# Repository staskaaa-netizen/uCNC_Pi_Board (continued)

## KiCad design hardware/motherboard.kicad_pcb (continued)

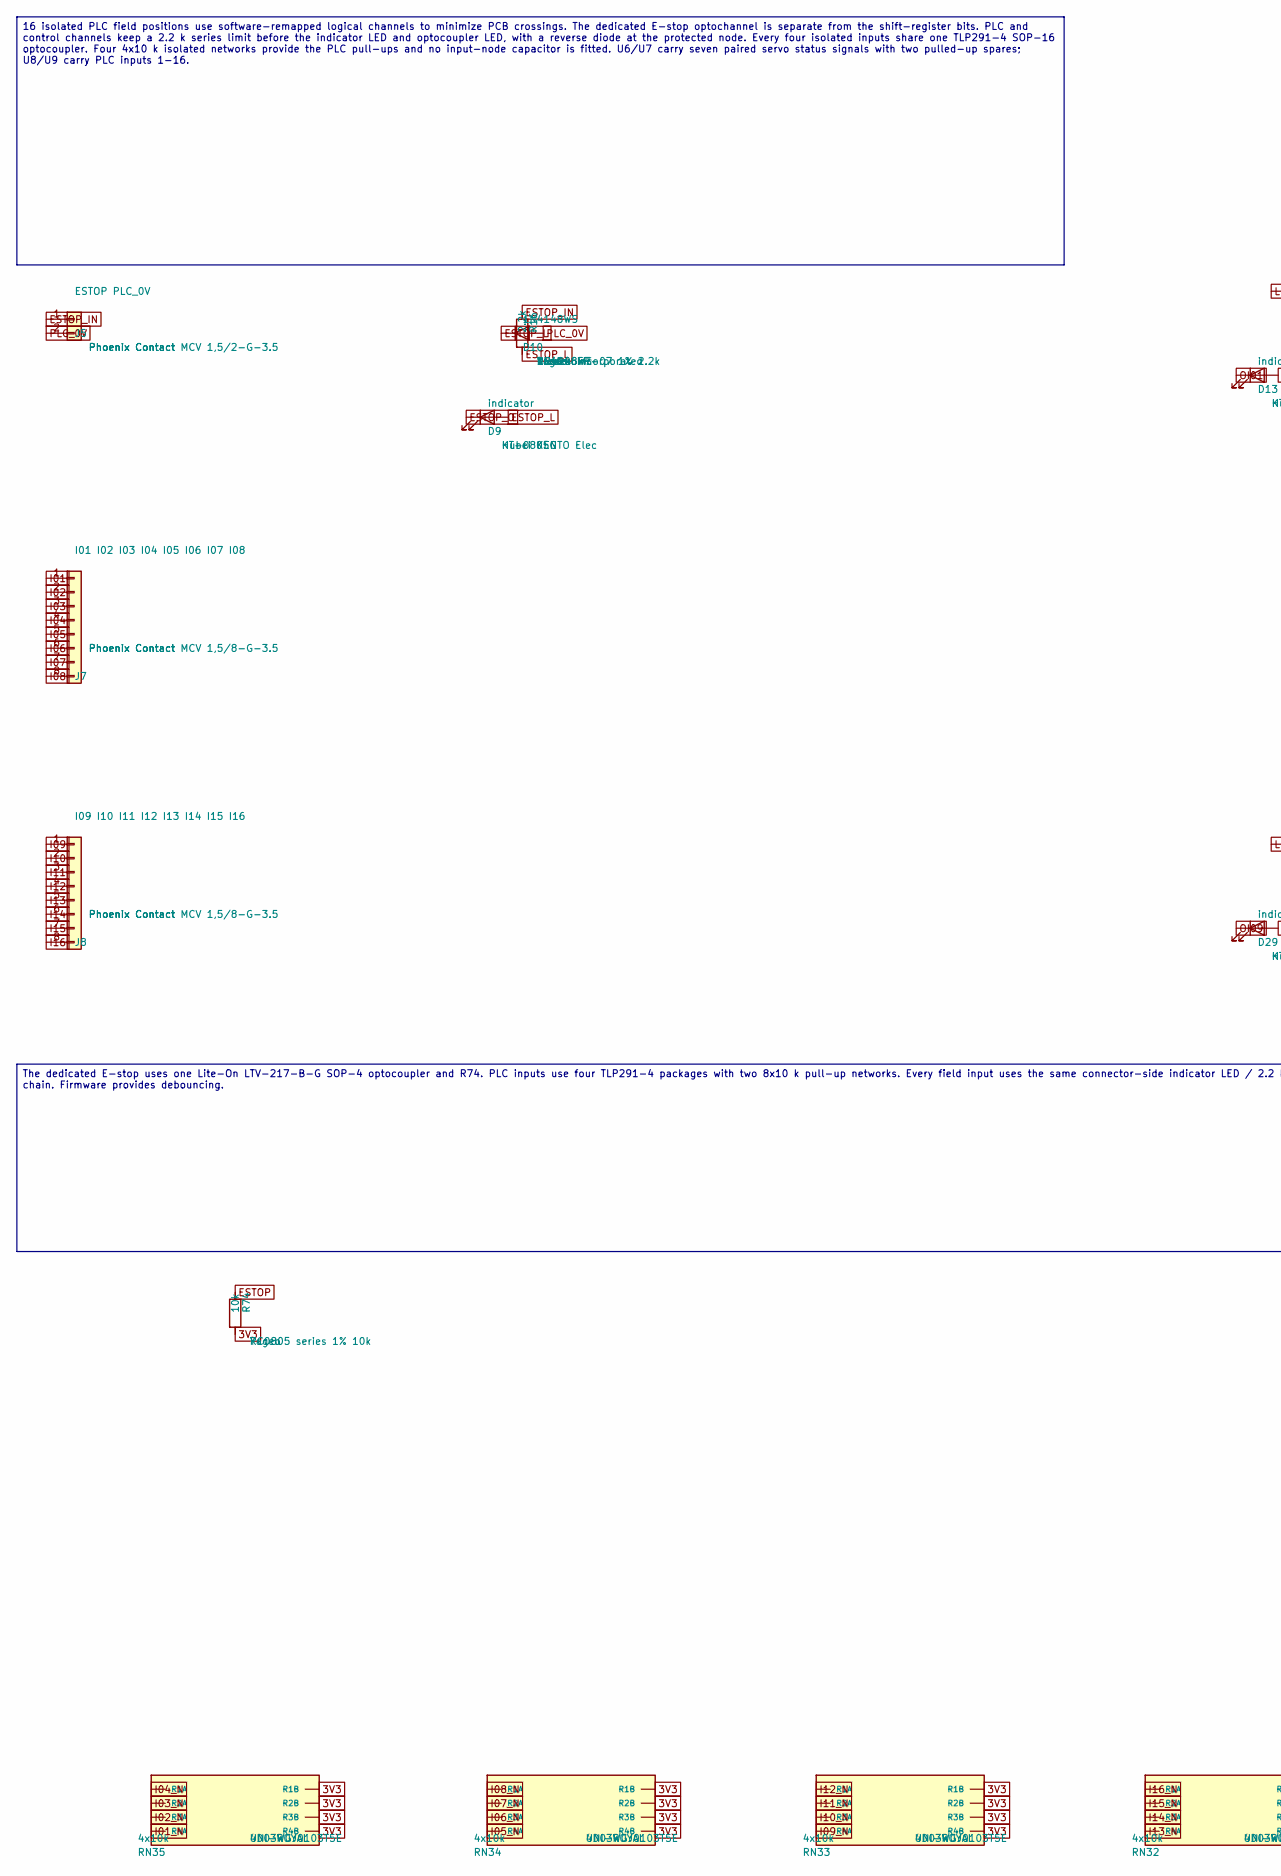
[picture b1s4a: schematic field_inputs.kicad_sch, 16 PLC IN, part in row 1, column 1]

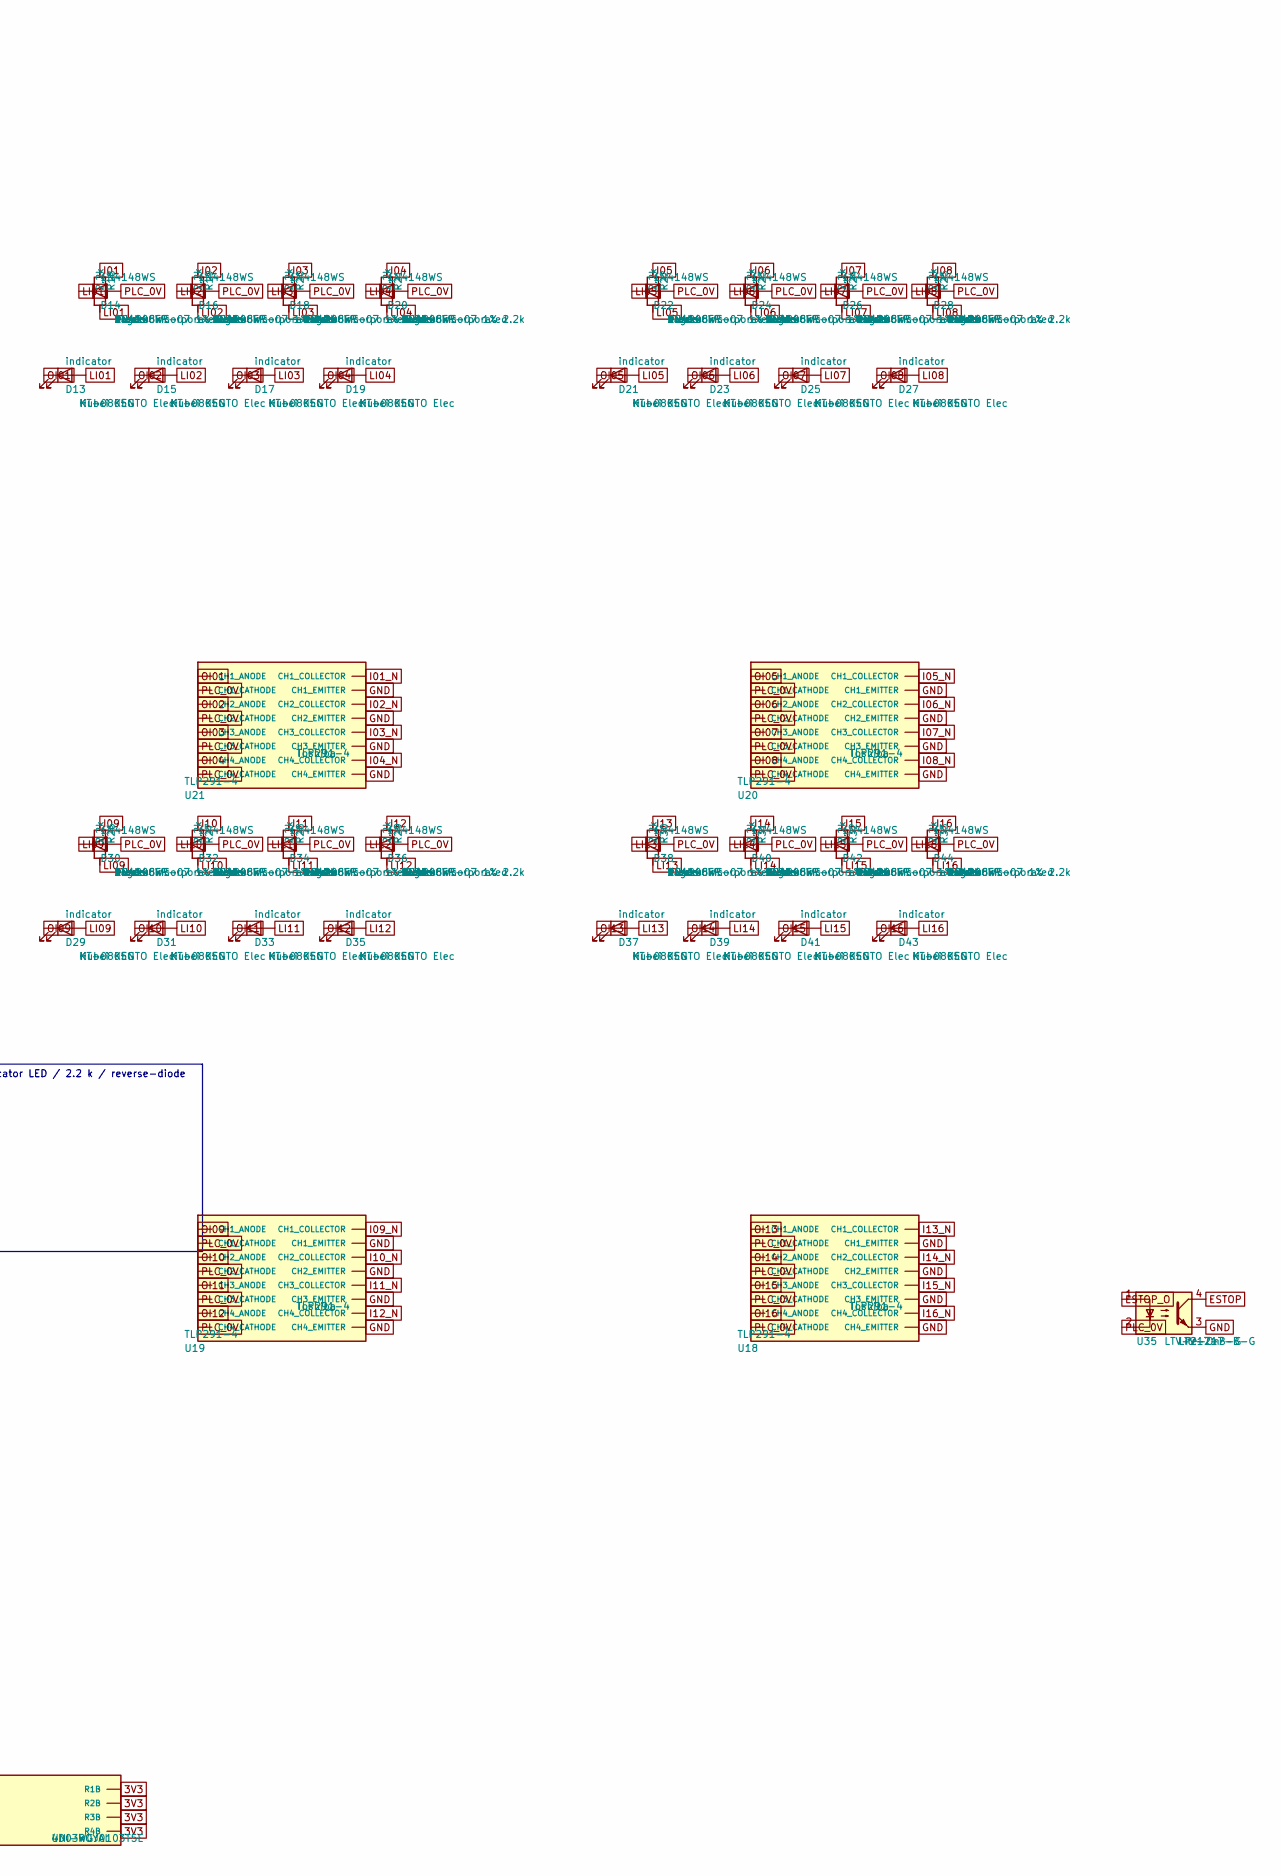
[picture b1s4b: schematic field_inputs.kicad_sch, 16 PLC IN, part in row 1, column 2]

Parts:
D9, D13, D15, D17, D19, D21, D23, D25, D27, D29, D31, D33, D35, D37, D39, D41, D43: indicator; LED_0805_2012Metric; MPN KT-0805G
D10, D14, D16, D18, D20, D22, D24, D26, D28, D30, D32, D34, D36, D38, D40, D42, D44: 1N4148WS; D_SOD-323; MPN 1N4148WS
J5: ESTOP PLC_0V; PhoenixContact_MCV_1,5_2-G-3.5_1x02_P3.50mm_Vertical; MPN Phoenix Contact MCV 1,5/2-G-3.5
J7: I01 I02 I03 I04 I05 I06 I07 I08; PhoenixContact_MCV_1,5_8-G-3.5_1x08_P3.50mm_Vertical; MPN Phoenix Contact MCV 1,5/8-G-3.5
J8: I09 I10 I11 I12 I13 I14 I15 I16; PhoenixContact_MCV_1,5_8-G-3.5_1x08_P3.50mm_Vertical; MPN Phoenix Contact MCV 1,5/8-G-3.5
R16, R18, R19, R20, R21, R22, R23, R24, R25, R26, R27, R28, R29, R30, R31, R32, R33: 2.2k; R_1206_3216Metric; MPN RC1206FR-07 1% 2.2k
R74: 10k; R_0805_2012Metric; MPN RC0805 series 1% 10k
RN32, RN33, RN34, RN35: 4x10k; R_Array_Convex_4x0603; MPN 4D03WGJ0103T5E
U18, U19, U20, U21: TLP291-4; SOIC-16_4.55x10.3mm_P1.27mm; MPN TLP291-4
U35: LTV-217-B-G; SOIC-4_4.55x2.6mm_P1.27mm; MPN LTV-217-B-G

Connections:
3V3: R74.2, RN32.5 (R4B), RN32.6 (R3B), RN32.7 (R2B), RN32.8 (R1B), RN33.5 (R4B), RN33.6 (R3B), RN33.7 (R2B), RN33.8 (R1B), RN34.5 (R4B), RN34.6 (R3B), RN34.7 (R2B), RN34.8 (R1B), RN35.5 (R4B), RN35.6 (R3B), RN35.7 (R2B), RN35.8 (R1B); also elsewhere on the board
ESTOP: R74.1, U35.4; also elsewhere on the board
ESTOP_IN: J5.1, R16.1
ESTOP_L: D9.2 (A), D10.1 (K), R16.2
ESTOP_O: D9.1 (K), U35.1
GND: U18.9 (CH4_EMITTER), U18.11 (CH3_EMITTER), U18.13 (CH2_EMITTER), U18.15 (CH1_EMITTER), U19.9 (CH4_EMITTER), U19.11 (CH3_EMITTER), U19.13 (CH2_EMITTER), U19.15 (CH1_EMITTER), U20.9 (CH4_EMITTER), U20.11 (CH3_EMITTER), U20.13 (CH2_EMITTER), U20.15 (CH1_EMITTER), U21.9 (CH4_EMITTER), U21.11 (CH3_EMITTER), U21.13 (CH2_EMITTER), U21.15 (CH1_EMITTER), U35.3; also elsewhere on the board
I01: J7.1, R18.1
I01_N: RN35.4 (R4A), U21.16 (CH1_COLLECTOR); also elsewhere on the board
I02: J7.2, R19.1
I02_N: RN35.3 (R3A), U21.14 (CH2_COLLECTOR); also elsewhere on the board
I03: J7.3, R20.1
I03_N: RN35.2 (R2A), U21.12 (CH3_COLLECTOR); also elsewhere on the board
I04: J7.4, R21.1
I04_N: RN35.1 (R1A), U21.10 (CH4_COLLECTOR); also elsewhere on the board
I05: J7.5, R22.1
I05_N: RN34.4 (R4A), U20.16 (CH1_COLLECTOR); also elsewhere on the board
I06: J7.6, R23.1
I06_N: RN34.3 (R3A), U20.14 (CH2_COLLECTOR); also elsewhere on the board
I07: J7.7, R24.1
I07_N: RN34.2 (R2A), U20.12 (CH3_COLLECTOR); also elsewhere on the board
I08: J7.8, R25.1
I08_N: RN34.1 (R1A), U20.10 (CH4_COLLECTOR); also elsewhere on the board
I09: J8.1, R26.1
I09_N: RN33.4 (R4A), U19.16 (CH1_COLLECTOR); also elsewhere on the board
I10: J8.2, R27.1
I10_N: RN33.3 (R3A), U19.14 (CH2_COLLECTOR); also elsewhere on the board
I11: J8.3, R28.1
I11_N: RN33.2 (R2A), U19.12 (CH3_COLLECTOR); also elsewhere on the board
I12: J8.4, R29.1
I12_N: RN33.1 (R1A), U19.10 (CH4_COLLECTOR); also elsewhere on the board
I13: J8.5, R30.1
I13_N: RN32.4 (R4A), U18.16 (CH1_COLLECTOR); also elsewhere on the board
I14: J8.6, R31.1
I14_N: RN32.3 (R3A), U18.14 (CH2_COLLECTOR); also elsewhere on the board
I15: J8.7, R32.1
I15_N: RN32.2 (R2A), U18.12 (CH3_COLLECTOR); also elsewhere on the board
I16: J8.8, R33.1
I16_N: RN32.1 (R1A), U18.10 (CH4_COLLECTOR); also elsewhere on the board
LI01: D13.2 (A), D14.1 (K), R18.2
LI02: D15.2 (A), D16.1 (K), R19.2
LI03: D17.2 (A), D18.1 (K), R20.2
LI04: D19.2 (A), D20.1 (K), R21.2
LI05: D21.2 (A), D22.1 (K), R22.2
LI06: D23.2 (A), D24.1 (K), R23.2
LI07: D25.2 (A), D26.1 (K), R24.2
LI08: D27.2 (A), D28.1 (K), R25.2
LI09: D29.2 (A), D30.1 (K), R26.2
LI10: D31.2 (A), D32.1 (K), R27.2
LI11: D33.2 (A), D34.1 (K), R28.2
LI12: D35.2 (A), D36.1 (K), R29.2
LI13: D37.2 (A), D38.1 (K), R30.2
LI14: D39.2 (A), D40.1 (K), R31.2
LI15: D41.2 (A), D42.1 (K), R32.2
LI16: D43.2 (A), D44.1 (K), R33.2
OI01: D13.1 (K), U21.1 (CH1_ANODE)
OI02: D15.1 (K), U21.3 (CH2_ANODE)
OI03: D17.1 (K), U21.5 (CH3_ANODE)
OI04: D19.1 (K), U21.7 (CH4_ANODE)
OI05: D21.1 (K), U20.1 (CH1_ANODE)
OI06: D23.1 (K), U20.3 (CH2_ANODE)
OI07: D25.1 (K), U20.5 (CH3_ANODE)
OI08: D27.1 (K), U20.7 (CH4_ANODE)
OI09: D29.1 (K), U19.1 (CH1_ANODE)
OI10: D31.1 (K), U19.3 (CH2_ANODE)
OI11: D33.1 (K), U19.5 (CH3_ANODE)
OI12: D35.1 (K), U19.7 (CH4_ANODE)
OI13: D37.1 (K), U18.1 (CH1_ANODE)
OI14: D39.1 (K), U18.3 (CH2_ANODE)
OI15: D41.1 (K), U18.5 (CH3_ANODE)
OI16: D43.1 (K), U18.7 (CH4_ANODE)
PLC_0V: D10.2 (A), D14.2 (A), D16.2 (A), D18.2 (A), D20.2 (A), D22.2 (A), D24.2 (A), D26.2 (A), D28.2 (A), D30.2 (A), D32.2 (A), D34.2 (A), D36.2 (A), D38.2 (A), D40.2 (A), D42.2 (A), D44.2 (A), J5.2, U18.2 (CH1_CATHODE), U18.4 (CH2_CATHODE), U18.6 (CH3_CATHODE), U18.8 (CH4_CATHODE), U19.2 (CH1_CATHODE), U19.4 (CH2_CATHODE), U19.6 (CH3_CATHODE), U19.8 (CH4_CATHODE), U20.2 (CH1_CATHODE), U20.4 (CH2_CATHODE), U20.6 (CH3_CATHODE), U20.8 (CH4_CATHODE), U21.2 (CH1_CATHODE), U21.4 (CH2_CATHODE), U21.6 (CH3_CATHODE), U21.8 (CH4_CATHODE), U35.2; also elsewhere on the board

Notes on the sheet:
16 isolated PLC field positions use software-remapped logical channels to minimize PCB crossings. The dedicated E-stop optochannel is separate from the shift-register bits. PLC and control channels keep a 2.2 k series limit before the indicator LED and optocoupler LED, with a reverse diode at the p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
The dedicated E-stop uses one Lite-On LTV-217-B-G SOP-4 optocoupler and R74. PLC inputs use four TLP291-4 packages with two 8x10 k pull-up networks. Every field input uses the same connector-side indicator LED / 2.2 k / reverse-diode chain. Firmware provides debouncing.

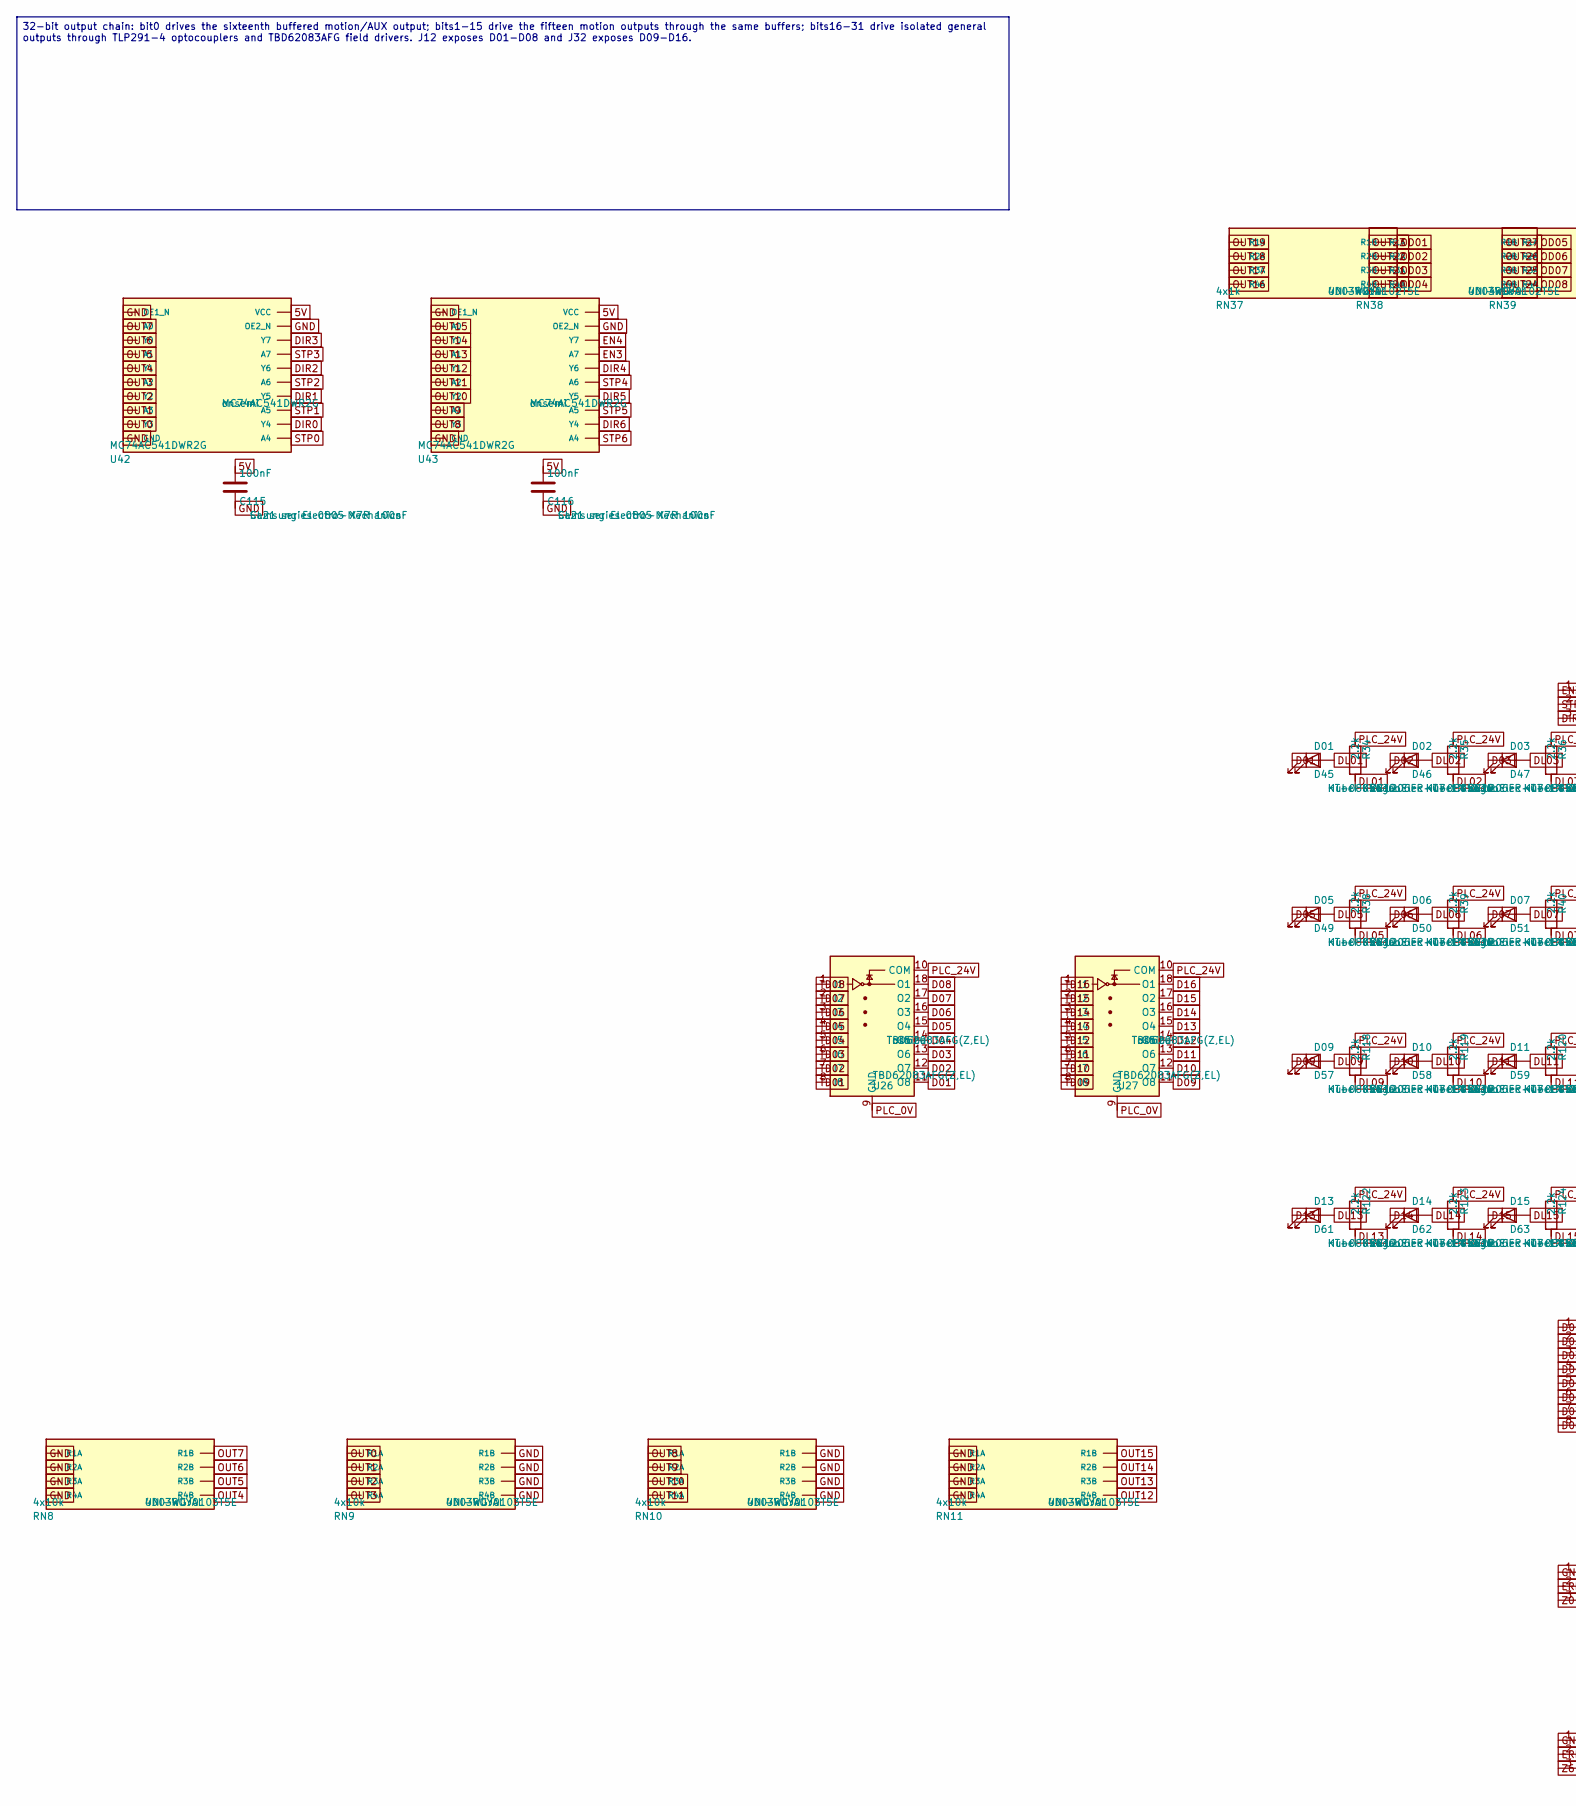
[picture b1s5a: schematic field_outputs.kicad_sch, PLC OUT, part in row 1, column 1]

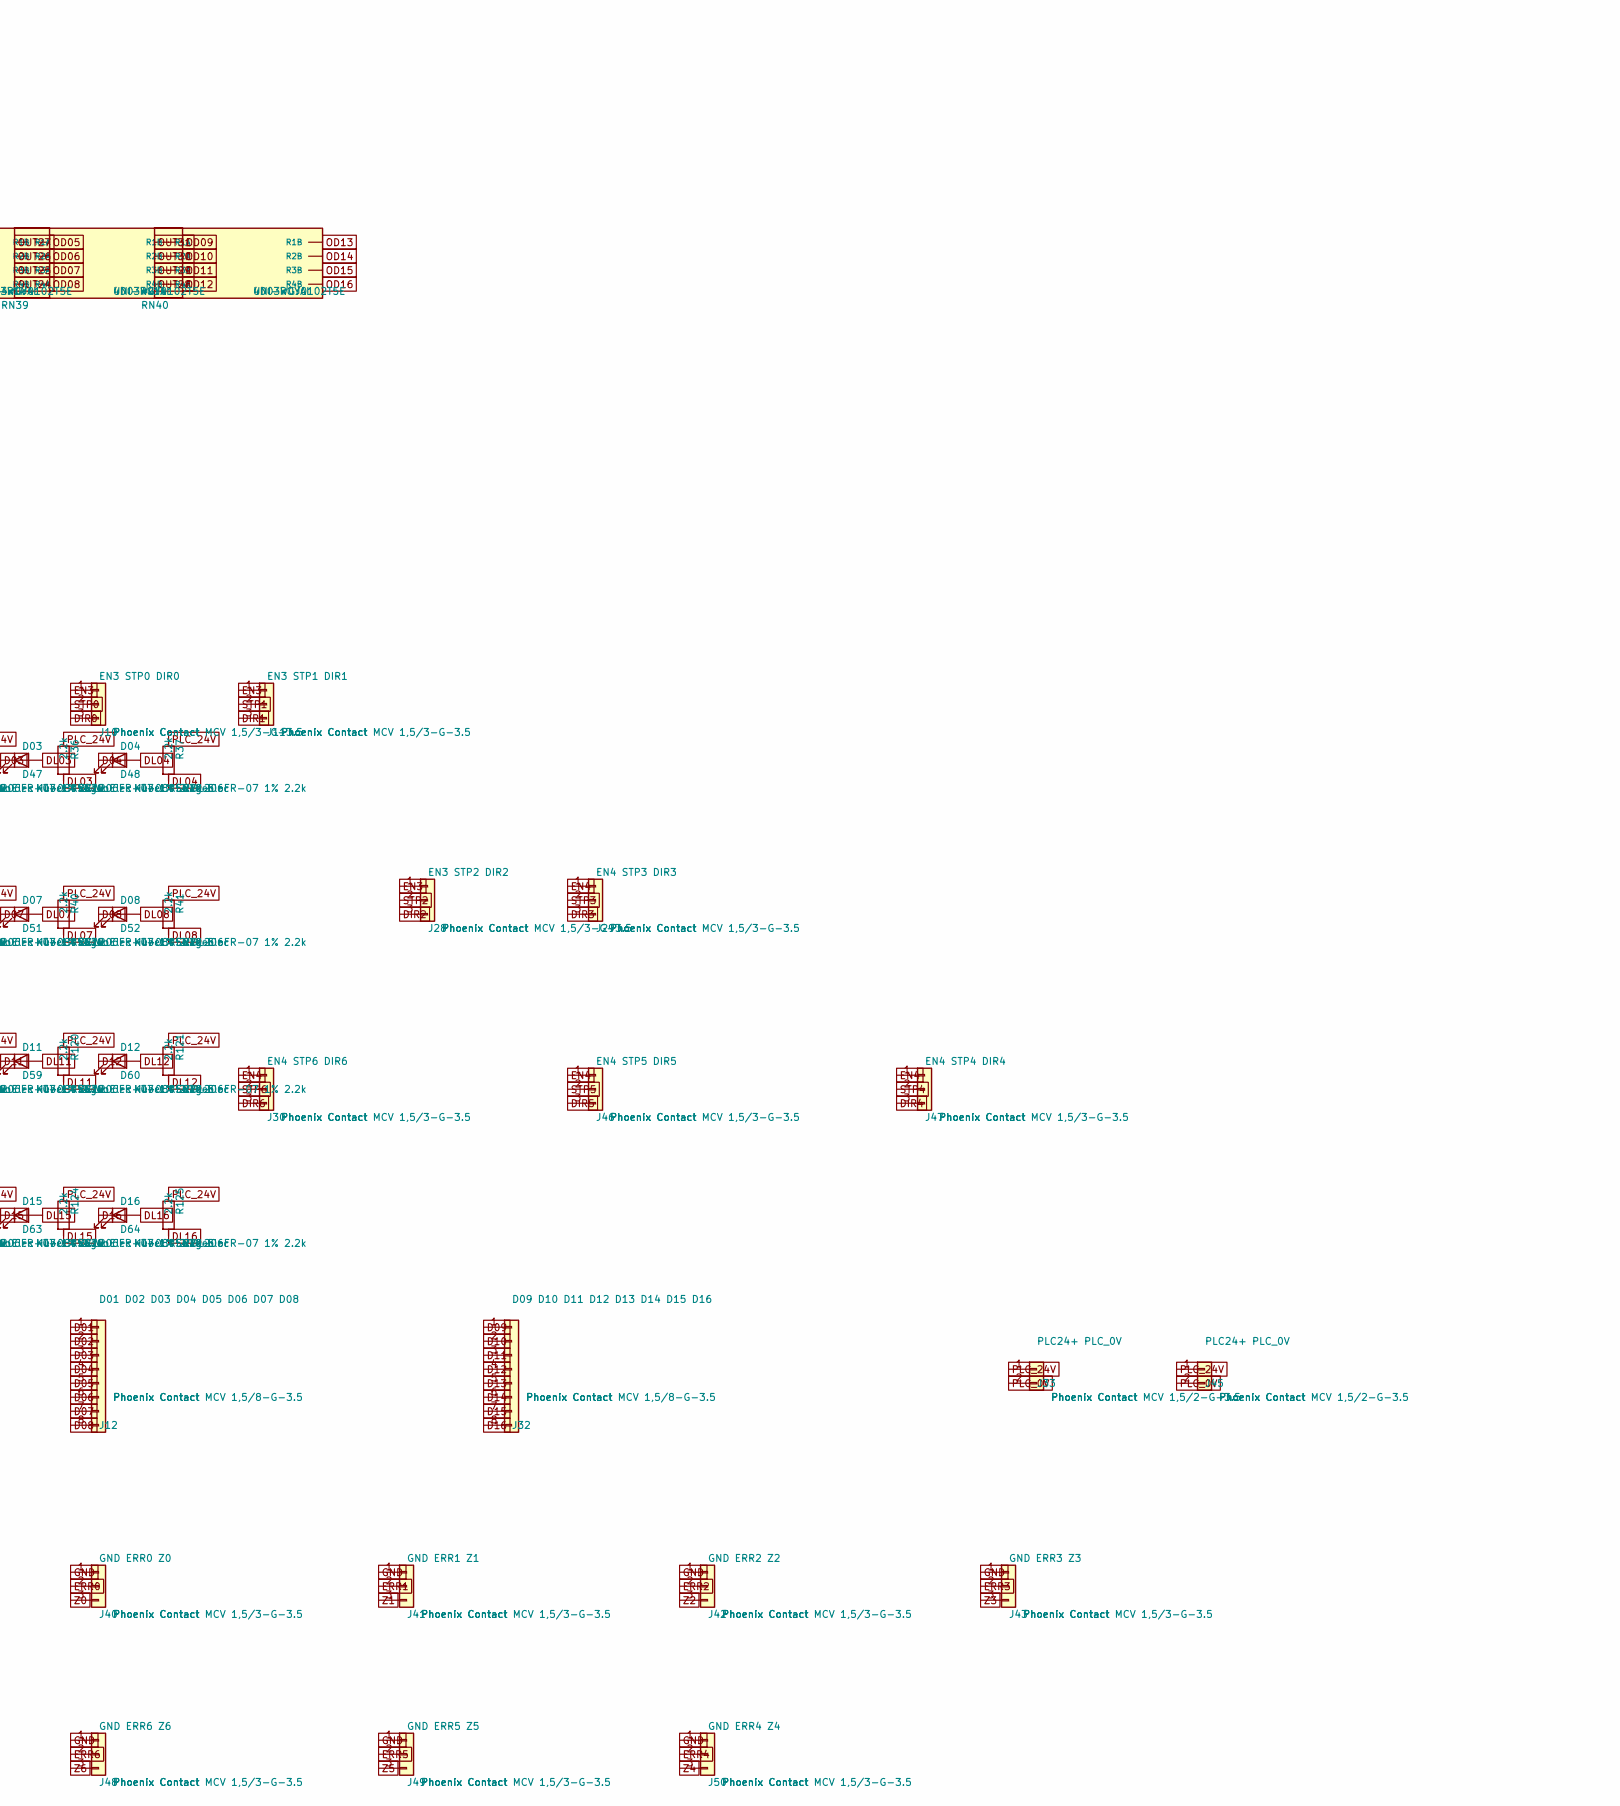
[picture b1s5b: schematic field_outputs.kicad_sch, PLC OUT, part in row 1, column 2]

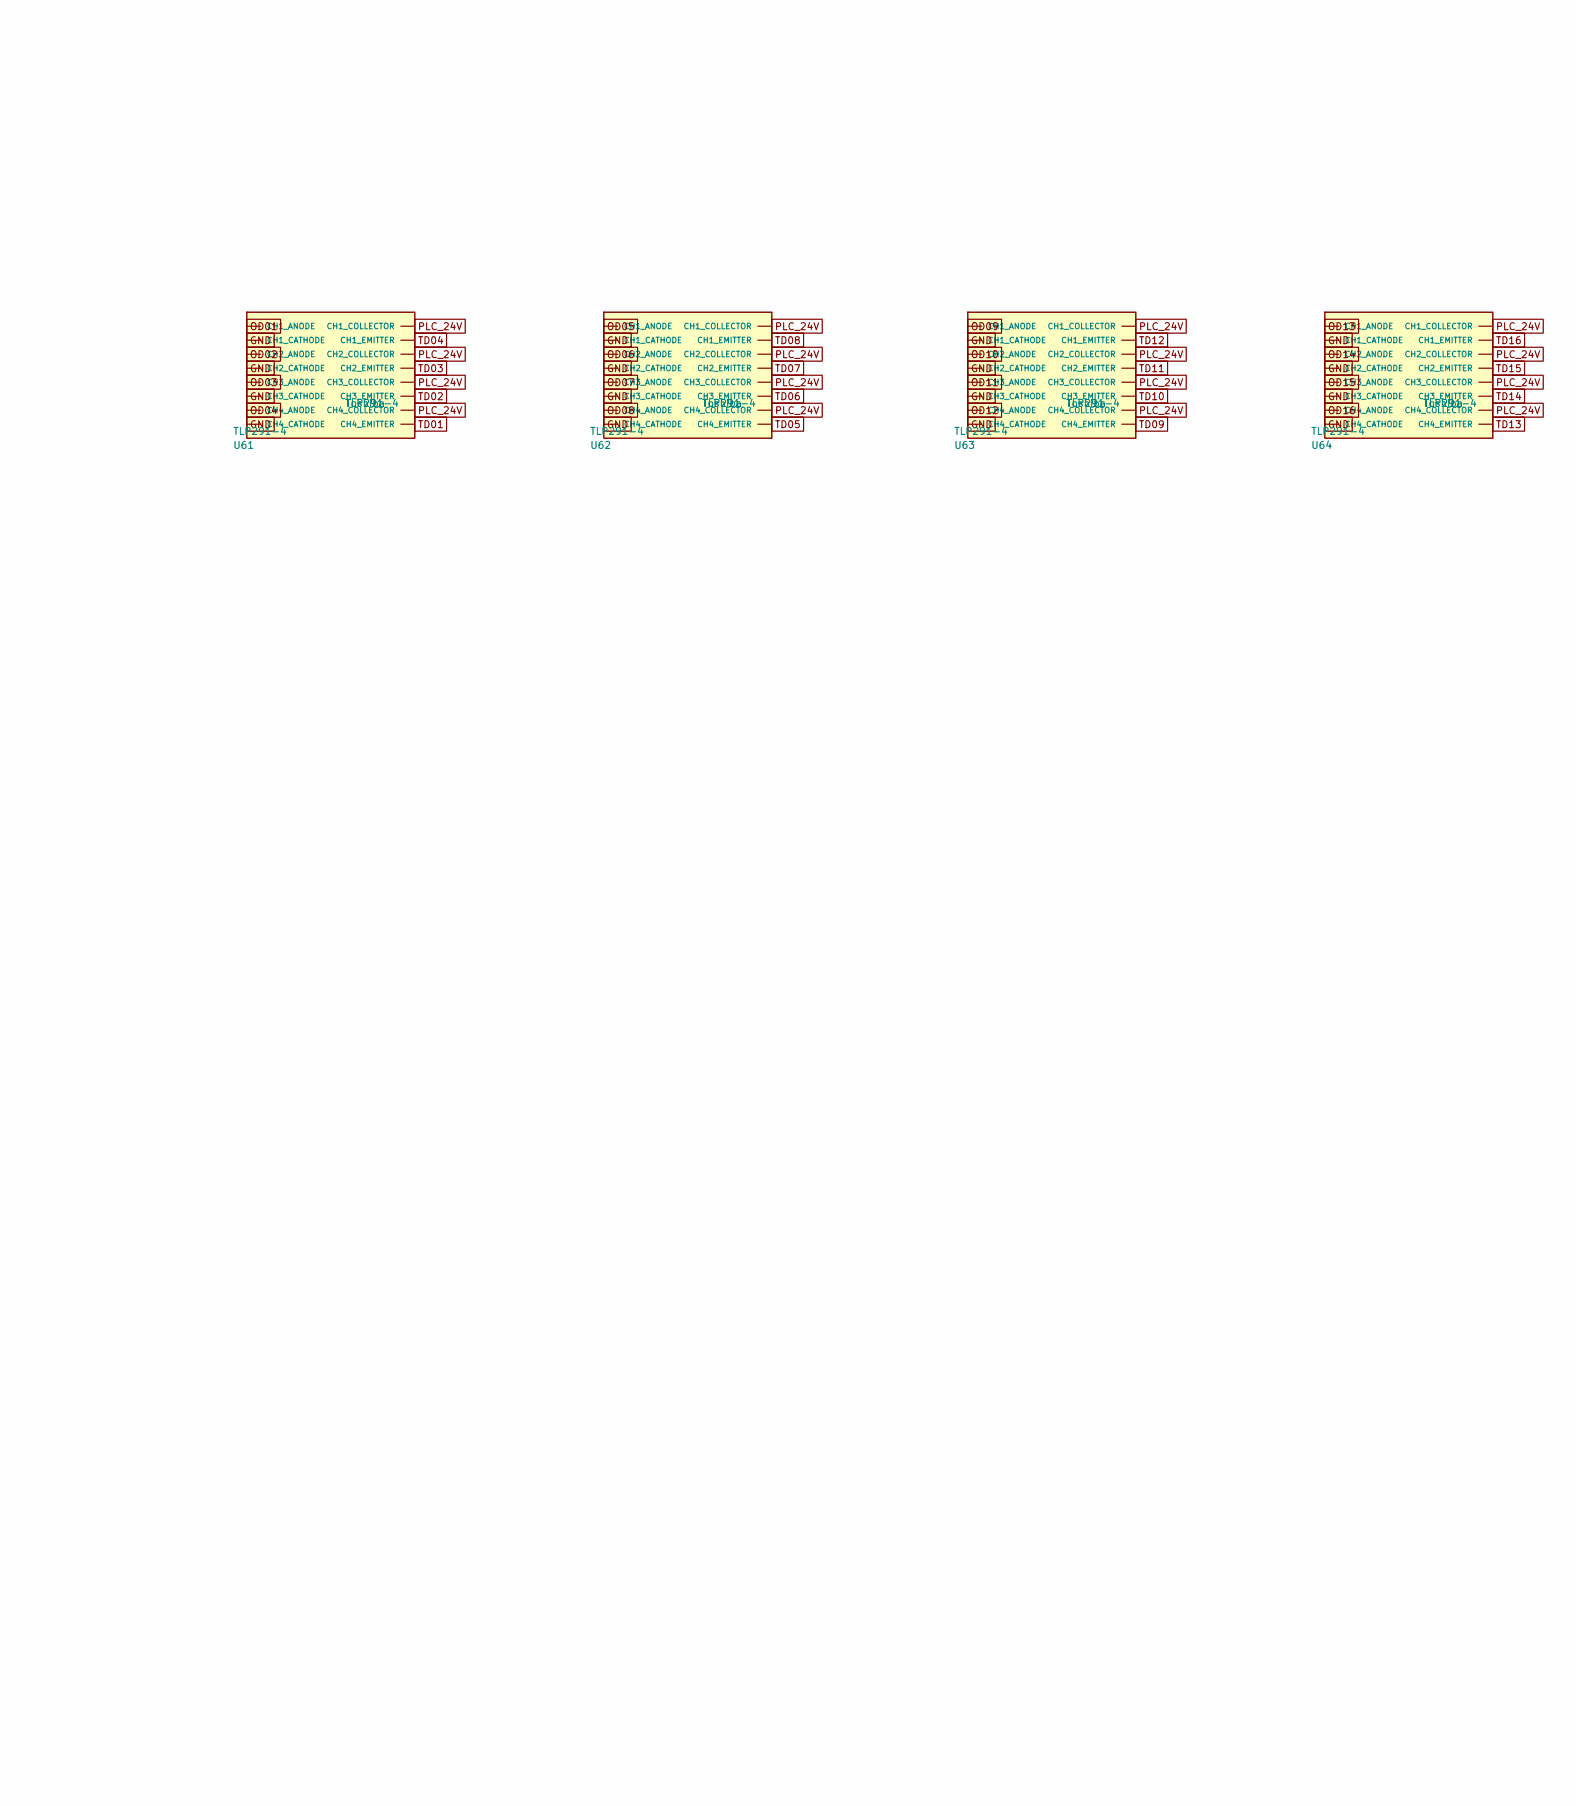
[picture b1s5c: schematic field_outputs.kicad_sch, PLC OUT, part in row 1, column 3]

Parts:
C115, C116: 100nF; C_0805_2012Metric; MPN CL21 series 0805 X7R 100nF
D45: D01; LED_0805_2012Metric; MPN KT-0805G
D46: D02; LED_0805_2012Metric; MPN KT-0805G
D47: D03; LED_0805_2012Metric; MPN KT-0805G
D48: D04; LED_0805_2012Metric; MPN KT-0805G
D49: D05; LED_0805_2012Metric; MPN KT-0805G
D50: D06; LED_0805_2012Metric; MPN KT-0805G
D51: D07; LED_0805_2012Metric; MPN KT-0805G
D52: D08; LED_0805_2012Metric; MPN KT-0805G
D57: D09; LED_0805_2012Metric; MPN KT-0805G
D58: D10; LED_0805_2012Metric; MPN KT-0805G
D59: D11; LED_0805_2012Metric; MPN KT-0805G
D60: D12; LED_0805_2012Metric; MPN KT-0805G
D61: D13; LED_0805_2012Metric; MPN KT-0805G
D62: D14; LED_0805_2012Metric; MPN KT-0805G
D63: D15; LED_0805_2012Metric; MPN KT-0805G
D64: D16; LED_0805_2012Metric; MPN KT-0805G
J10: EN3 STP0 DIR0; PhoenixContact_MCV_1,5_3-G-3.5_1x03_P3.50mm_Vertical; MPN Phoenix Contact MCV 1,5/3-G-3.5
J11: EN3 STP1 DIR1; PhoenixContact_MCV_1,5_3-G-3.5_1x03_P3.50mm_Vertical; MPN Phoenix Contact MCV 1,5/3-G-3.5
J12: D01 D02 D03 D04 D05 D06 D07 D08; PhoenixContact_MCV_1,5_8-G-3.5_1x08_P3.50mm_Vertical; MPN Phoenix Contact MCV 1,5/8-G-3.5
J28: EN3 STP2 DIR2; PhoenixContact_MCV_1,5_3-G-3.5_1x03_P3.50mm_Vertical; MPN Phoenix Contact MCV 1,5/3-G-3.5
J29: EN4 STP3 DIR3; PhoenixContact_MCV_1,5_3-G-3.5_1x03_P3.50mm_Vertical; MPN Phoenix Contact MCV 1,5/3-G-3.5
J30: EN4 STP6 DIR6; PhoenixContact_MCV_1,5_3-G-3.5_1x03_P3.50mm_Vertical; MPN Phoenix Contact MCV 1,5/3-G-3.5
J32: D09 D10 D11 D12 D13 D14 D15 D16; PhoenixContact_MCV_1,5_8-G-3.5_1x08_P3.50mm_Vertical; MPN Phoenix Contact MCV 1,5/8-G-3.5
J33, J45: PLC24+ PLC_0V; PhoenixContact_MCV_1,5_2-G-3.5_1x02_P3.50mm_Vertical; MPN Phoenix Contact MCV 1,5/2-G-3.5
J40: GND ERR0 Z0; PhoenixContact_MCV_1,5_3-G-3.5_1x03_P3.50mm_Vertical; MPN Phoenix Contact MCV 1,5/3-G-3.5
J41: GND ERR1 Z1; PhoenixContact_MCV_1,5_3-G-3.5_1x03_P3.50mm_Vertical; MPN Phoenix Contact MCV 1,5/3-G-3.5
J42: GND ERR2 Z2; PhoenixContact_MCV_1,5_3-G-3.5_1x03_P3.50mm_Vertical; MPN Phoenix Contact MCV 1,5/3-G-3.5
J43: GND ERR3 Z3; PhoenixContact_MCV_1,5_3-G-3.5_1x03_P3.50mm_Vertical; MPN Phoenix Contact MCV 1,5/3-G-3.5
J46: EN4 STP5 DIR5; PhoenixContact_MCV_1,5_3-G-3.5_1x03_P3.50mm_Vertical; MPN Phoenix Contact MCV 1,5/3-G-3.5
J47: EN4 STP4 DIR4; PhoenixContact_MCV_1,5_3-G-3.5_1x03_P3.50mm_Vertical; MPN Phoenix Contact MCV 1,5/3-G-3.5
J48: GND ERR6 Z6; PhoenixContact_MCV_1,5_3-G-3.5_1x03_P3.50mm_Vertical; MPN Phoenix Contact MCV 1,5/3-G-3.5
J49: GND ERR5 Z5; PhoenixContact_MCV_1,5_3-G-3.5_1x03_P3.50mm_Vertical; MPN Phoenix Contact MCV 1,5/3-G-3.5
J50: GND ERR4 Z4; PhoenixContact_MCV_1,5_3-G-3.5_1x03_P3.50mm_Vertical; MPN Phoenix Contact MCV 1,5/3-G-3.5
R34, R35, R36, R37, R38, R39, R40, R41, R118, R119, R120, R121, R122, R123, R124, R125: 2.2k; R_1206_3216Metric; MPN RC1206FR-07 1% 2.2k
RN8, RN9, RN10, RN11: 4x10k; R_Array_Convex_4x0603; MPN 4D03WGJ0103T5E
RN37, RN38, RN39, RN40: 4x1k; R_Array_Convex_4x0603; MPN 4D03WGJ0102T5E
U26, U27: TBD62083AFG(Z,EL); SOP-18_7.495x11.515mm_P1.27mm; MPN TBD62083AFG(Z,EL)
U42, U43: MC74AC541DWR2G; SOIC-20W_7.5x12.8mm_P1.27mm; MPN MC74AC541DWR2G
U61, U62, U63, U64: TLP291-4; SOIC-16_4.55x10.3mm_P1.27mm; MPN TLP291-4

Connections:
5V: C115.1, C116.1, U42.20 (VCC), U43.20 (VCC); also elsewhere on the board
D01: D45.1 (K), J12.1, U26.11 (O8)
D02: D46.1 (K), J12.2, U26.12 (O7)
D03: D47.1 (K), J12.3, U26.13 (O6)
D04: D48.1 (K), J12.4, U26.14 (O5)
D05: D49.1 (K), J12.5, U26.15 (O4)
D06: D50.1 (K), J12.6, U26.16 (O3)
D07: D51.1 (K), J12.7, U26.17 (O2)
D08: D52.1 (K), J12.8, U26.18 (O1)
D09: D57.1 (K), J32.1, U27.11 (O8)
D10: D58.1 (K), J32.2, U27.12 (O7)
D11: D59.1 (K), J32.3, U27.13 (O6)
D12: D60.1 (K), J32.4, U27.14 (O5)
D13: D61.1 (K), J32.5, U27.15 (O4)
D14: D62.1 (K), J32.6, U27.16 (O3)
D15: D63.1 (K), J32.7, U27.17 (O2)
D16: D64.1 (K), J32.8, U27.18 (O1)
DIR0: J10.3, U42.12 (Y4)
DIR1: J11.3, U42.14 (Y5)
DIR2: J28.3, U42.16 (Y6)
DIR3: J29.3, U42.18 (Y7)
DIR4: J47.3, U43.16 (Y6)
DIR5: J46.3, U43.14 (Y5)
DIR6: J30.3, U43.12 (Y4)
DL01: D45.2 (A), R34.2
DL02: D46.2 (A), R35.2
DL03: D47.2 (A), R36.2
DL04: D48.2 (A), R37.2
DL05: D49.2 (A), R38.2
DL06: D50.2 (A), R39.2
DL07: D51.2 (A), R40.2
DL08: D52.2 (A), R41.2
DL09: D57.2 (A), R118.2
DL10: D58.2 (A), R119.2
DL11: D59.2 (A), R120.2
DL12: D60.2 (A), R121.2
DL13: D61.2 (A), R122.2
DL14: D62.2 (A), R123.2
DL15: D63.2 (A), R124.2
DL16: D64.2 (A), R125.2
EN3: J10.1, J11.1, J28.1, U43.17 (A7)
EN4: J29.1, J30.1, J46.1, J47.1, U43.18 (Y7)
ERR0: J40.2; also elsewhere on the board
ERR1: J41.2; also elsewhere on the board
ERR2: J42.2; also elsewhere on the board
ERR3: J43.2; also elsewhere on the board
ERR4: J50.2; also elsewhere on the board
ERR5: J49.2; also elsewhere on the board
ERR6: J48.2; also elsewhere on the board
GND: C115.2, C116.2, J40.1, J41.1, J42.1, J43.1, J48.1, J49.1, J50.1, RN8.1 (R1A), RN8.2 (R2A), RN8.3 (R3A), RN8.4 (R4A), RN9.5 (R4B), RN9.6 (R3B), RN9.7 (R2B), RN9.8 (R1B), RN10.5 (R4B), RN10.6 (R3B), RN10.7 (R2B), RN10.8 (R1B), RN11.1 (R1A), RN11.2 (R2A), RN11.3 (R3A), RN11.4 (R4A), U42.1 (OE1_N), U42.10 (GND), U42.19 (OE2_N), U43.1 (OE1_N), U43.10 (GND), U43.19 (OE2_N), U61.2 (CH1_CATHODE), U61.4 (CH2_CATHODE), U61.6 (CH3_CATHODE), U61.8 (CH4_CATHODE), U62.2 (CH1_CATHODE), U62.4 (CH2_CATHODE), U62.6 (CH3_CATHODE), U62.8 (CH4_CATHODE), U63.2 (CH1_CATHODE), U63.4 (CH2_CATHODE), U63.6 (CH3_CATHODE), U63.8 (CH4_CATHODE), U64.2 (CH1_CATHODE), U64.4 (CH2_CATHODE), U64.6 (CH3_CATHODE), U64.8 (CH4_CATHODE); also elsewhere on the board
OD01: RN37.8 (R1B), U61.1 (CH1_ANODE)
OD02: RN37.7 (R2B), U61.3 (CH2_ANODE)
OD03: RN37.6 (R3B), U61.5 (CH3_ANODE)
OD04: RN37.5 (R4B), U61.7 (CH4_ANODE)
OD05: RN38.8 (R1B), U62.1 (CH1_ANODE)
OD06: RN38.7 (R2B), U62.3 (CH2_ANODE)
OD07: RN38.6 (R3B), U62.5 (CH3_ANODE)
OD08: RN38.5 (R4B), U62.7 (CH4_ANODE)
OD09: RN39.8 (R1B), U63.1 (CH1_ANODE)
OD10: RN39.7 (R2B), U63.3 (CH2_ANODE)
OD11: RN39.6 (R3B), U63.5 (CH3_ANODE)
OD12: RN39.5 (R4B), U63.7 (CH4_ANODE)
OD13: RN40.8 (R1B), U64.1 (CH1_ANODE)
OD14: RN40.7 (R2B), U64.3 (CH2_ANODE)
OD15: RN40.6 (R3B), U64.5 (CH3_ANODE)
OD16: RN40.5 (R4B), U64.7 (CH4_ANODE)
OUT0: RN9.1 (R1A), U42.9 (Y3); also elsewhere on the board
OUT1: RN9.2 (R2A), U42.8 (A3); also elsewhere on the board
OUT2: RN9.3 (R3A), U42.7 (Y2); also elsewhere on the board
OUT3: RN9.4 (R4A), U42.6 (A2); also elsewhere on the board
OUT4: RN8.5 (R4B), U42.5 (Y1); also elsewhere on the board
OUT5: RN8.6 (R3B), U42.4 (A1); also elsewhere on the board
OUT6: RN8.7 (R2B), U42.3 (Y0); also elsewhere on the board
OUT7: RN8.8 (R1B), U42.2 (A0); also elsewhere on the board
OUT8: RN10.1 (R1A), U43.9 (Y3); also elsewhere on the board
OUT9: RN10.2 (R2A), U43.8 (A3); also elsewhere on the board
OUT10: RN10.3 (R3A), U43.7 (Y2); also elsewhere on the board
OUT11: RN10.4 (R4A), U43.6 (A2); also elsewhere on the board
OUT12: RN11.5 (R4B), U43.5 (Y1); also elsewhere on the board
OUT13: RN11.6 (R3B), U43.4 (A1); also elsewhere on the board
OUT14: RN11.7 (R2B), U43.3 (Y0); also elsewhere on the board
OUT15: RN11.8 (R1B), U43.2 (A0); also elsewhere on the board
OUT16: RN37.4 (R4A); also elsewhere on the board
OUT17: RN37.3 (R3A); also elsewhere on the board
OUT18: RN37.2 (R2A); also elsewhere on the board
OUT19: RN37.1 (R1A); also elsewhere on the board
OUT20: RN38.4 (R4A); also elsewhere on the board
OUT21: RN38.3 (R3A); also elsewhere on the board
OUT22: RN38.2 (R2A); also elsewhere on the board
OUT23: RN38.1 (R1A); also elsewhere on the board
OUT24: RN39.4 (R4A); also elsewhere on the board
OUT25: RN39.3 (R3A); also elsewhere on the board
OUT26: RN39.2 (R2A); also elsewhere on the board
OUT27: RN39.1 (R1A); also elsewhere on the board
OUT28: RN40.4 (R4A); also elsewhere on the board
OUT29: RN40.3 (R3A); also elsewhere on the board
OUT30: RN40.2 (R2A); also elsewhere on the board
OUT31: RN40.1 (R1A); also elsewhere on the board
PLC_0V: J33.2, J45.2, U26.9 (GND), U27.9 (GND); also elsewhere on the board
PLC_24V: J33.1, J45.1, R34.1, R35.1, R36.1, R37.1, R38.1, R39.1, R40.1, R41.1, R118.1, R119.1, R120.1, R121.1, R122.1, R123.1, R124.1, R125.1, U26.10 (COM), U27.10 (COM), U61.10 (CH4_COLLECTOR), U61.12 (CH3_COLLECTOR), U61.14 (CH2_COLLECTOR), U61.16 (CH1_COLLECTOR), U62.10 (CH4_COLLECTOR), U62.12 (CH3_COLLECTOR), U62.14 (CH2_COLLECTOR), U62.16 (CH1_COLLECTOR), U63.10 (CH4_COLLECTOR), U63.12 (CH3_COLLECTOR), U63.14 (CH2_COLLECTOR), U63.16 (CH1_COLLECTOR), U64.10 (CH4_COLLECTOR), U64.12 (CH3_COLLECTOR), U64.14 (CH2_COLLECTOR), U64.16 (CH1_COLLECTOR); also elsewhere on the board
STP0: J10.2, U42.11 (A4)
STP1: J11.2, U42.13 (A5)
STP2: J28.2, U42.15 (A6)
STP3: J29.2, U42.17 (A7)
STP4: J47.2, U43.15 (A6)
STP5: J46.2, U43.13 (A5)
STP6: J30.2, U43.11 (A4)
TD01: U26.8 (I8), U61.9 (CH4_EMITTER)
TD02: U26.7 (I7), U61.11 (CH3_EMITTER)
TD03: U26.6 (I6), U61.13 (CH2_EMITTER)
TD04: U26.5 (I5), U61.15 (CH1_EMITTER)
TD05: U26.4 (I4), U62.9 (CH4_EMITTER)
TD06: U26.3 (I3), U62.11 (CH3_EMITTER)
TD07: U26.2 (I2), U62.13 (CH2_EMITTER)
TD08: U26.1 (I1), U62.15 (CH1_EMITTER)
TD09: U27.8 (I8), U63.9 (CH4_EMITTER)
TD10: U27.7 (I7), U63.11 (CH3_EMITTER)
TD11: U27.6 (I6), U63.13 (CH2_EMITTER)
TD12: U27.5 (I5), U63.15 (CH1_EMITTER)
TD13: U27.4 (I4), U64.9 (CH4_EMITTER)
TD14: U27.3 (I3), U64.11 (CH3_EMITTER)
TD15: U27.2 (I2), U64.13 (CH2_EMITTER)
TD16: U27.1 (I1), U64.15 (CH1_EMITTER)
Z0: J40.3; also elsewhere on the board
Z1: J41.3; also elsewhere on the board
Z2: J42.3; also elsewhere on the board
Z3: J43.3; also elsewhere on the board
Z4: J50.3; also elsewhere on the board
Z5: J49.3; also elsewhere on the board
Z6: J48.3; also elsewhere on the board

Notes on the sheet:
32-bit output chain: bit0 drives the sixteenth buffered motion/AUX output; bits1-15 drive the fifteen motion outputs through the same buffers; bits16-31 drive isolated general outputs through TLP291-4 optocouplers and TBD62083AFG field drivers. J12 exposes D01-D08 and J32 exposes D09-D16.
